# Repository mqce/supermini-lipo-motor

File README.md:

# supermini-lipo-motor

ESP32-C3 SuperMini の下に重ねる、2 モーター駆動と LiPo 充電の拡張基板です。外形は 18 × 24 mm、2 層です。回路図のリビジョンは 1（2026-11-01）です。

SuperMini のピンヘッダ（2.54 mm、左右 1×8）に合わせたスルーホールで接続します。電池、電源スイッチ、モーターは基板端の手はんだパッド（1.5 mm ピッチ、ドリル 0.7 mm）へ配線します。

## 電源

| ネット | 役割 |
| --- | --- |
| V5 | SuperMini の 5V。TP4056 の入力（USB 充電） |
| VBAT | LiPo 正極。TP4056 の BAT |
| VSW | モータードライバの電源。外部スイッチの負荷側 |
| GND | 共通グランド |

J3 の `SW_BAT`（VBAT）と `SW_LOAD`（VSW）のあいだに電源スイッチを入れます。スイッチを入れると電池が TC118S に供給されます。

D1（B5819W）はカソードが V5、アノードが VSW です。スイッチオンのとき電池から SuperMini の 5V ピンへ給電し、USB の 5V はモーター電源へ流れません。

TP4056 の PROG は 10 kΩ で、充電電流は約 120 mA です。CE は VCC、TEMP は GND に接続しています。充電中は LED1（赤）が点灯します。

## モーター

ドライバは Fuman TC118S が 2 個です。入力は 100 Ω を直列に入れています。

| モーター | INA | INB |
| --- | --- | --- |
| M1 | GPIO4 | GPIO3 |
| M2 | GPIO10 | GPIO7 |

GPIO2、GPIO8、GPIO9 は ESP32-C3 のストラップピンです。駆動に使わないでください。

## 手はんだパッド（J3、左から）

1. BAT+
2. BAT-
3. SW_BAT（VBAT）
4. SW_LOAD（VSW）
5. M1+
6. M1-
7. M2+
8. M2-

USB 側が基板の +Y 端です。部品面を上、USB を上にしたとき、5V 列が左側、GPIO5 列が右側です。

## ファイル

| パス | 内容 |
| --- | --- |
| `supermini-lipo-motor.kicad_pro` | KiCad 10 プロジェクト |
| `symbols/` `footprints/` | 独自シンボルとワイヤパッド |
| `tools/build_board.py` | 回路図・基板・BOM の生成スクリプト |
| `fabrication/` | JLCPCB 向け Gerber、BOM、座標 |
| `production/` | 製造データの別書き出し |

KiCad 10 で `supermini-lipo-motor.kicad_pro` を開きます。生成し直す場合は、KiCad 10 の `pcbnew` が使える Python で `tools/build_board.py` を実行します。スクリプト内のパスはローカル環境向けです。

JLCPCB へ出すときは `fabrication/jlcpcb-gerber.zip` と `fabrication/bom.csv`、`fabrication/cpl.csv` を使います。ヘッダ J1/J2 とワイヤパッド J3 は BOM に含まれません。

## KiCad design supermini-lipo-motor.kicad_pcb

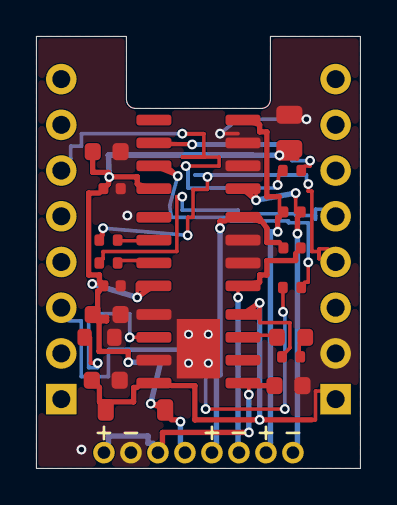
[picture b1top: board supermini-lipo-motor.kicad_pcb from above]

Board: 2 copper layers, 18.0 x 24.0 mm, 23 parts (0 on the bottom side), 19 nets.

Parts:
C1, C2, C3, C5: 10uF; C_0603_1608Metric
C4, C6, C7, C8: 100nF; C_0402_1005Metric
C9: 22uF; C_0805_2012Metric
D1: B5819W; D_SOD-123
J1: ESP_L; PTH_1x08_P2.54mm
J2: ESP_R; PTH_1x08_P2.54mm
J3: WIRES
LED1: RED; LED_0603_1608Metric
R1: 10k; R_0603_1608Metric
R2: 1k; R_0402_1005Metric
R3, R4, R5, R6: 100; R_0402_1005Metric
U1, U2: TC118S; SOIC-8_3.9x4.9mm_P1.27mm
U3: TP4056; SOIC-8-1EP_3.9x4.9mm_P1.27mm_EP2.41x3.3mm

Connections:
CHRG: LED1.1, U3.7
GND: C1.2, C2.2, C3.2, C4.2, C5.2, C6.2, C9.2, J1.2, J3.2, R1.2, U1.6, U1.7, U2.6, U2.7, U3.1, U3.3, U3.9
GPIO3: J1.5, R4.1
GPIO4: J1.4, R3.1
GPIO7: J2.3, R6.1
GPIO10: J2.6, R5.1
LED_A: LED1.2, R2.2
M1+: C7.1, J3.5, U1.8
M1-: C7.2, J3.6, U1.5
M1_INA: R3.2, U1.2
M1_INB: R4.2, U1.3
M2+: C8.1, J3.7, U2.8
M2-: C8.2, J3.8, U2.5
M2_INA: R5.2, U2.2
M2_INB: R6.2, U2.3
PROG: R1.1, U3.2
V5: C1.1, D1.1, J1.1, R2.1, U3.4, U3.8
VBAT: C2.1, J3.1, J3.3, U3.5
VSW: C3.1, C4.1, C5.1, C6.1, C9.1, D1.2, J3.4, U1.4, U2.4

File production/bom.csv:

Designator,Footprint,Quantity,Value,LCSC Part #
"C1, C2, C3, C5",0603,4,10uF,
"C4, C6, C7, C8",0402,4,100nF,
C9,0805,1,22uF,
D1,D_SOD-123,1,B5819W,
LED1,0603,1,RED,
R1,0603,1,10k,
R2,0402,1,1k,
"R3, R4, R5, R6",0402,4,100,
"U1, U2",SOIC-8_3.9x4.9mm_P1.27mm,2,TC118S,
U3,SOIC-8-1EP_3.9x4.9mm_P1.27mm_EP2.41x3.3mm,1,TP4056,

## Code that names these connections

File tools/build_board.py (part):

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                ("1", "5V", "passive"),
                ("2", "GND", "passive"),
                ("3", "3V3", "passive"),
                ("4", "GPIO4", "output"),
                ("5", "GPIO3", "output"),
                ("6", "GPIO2", "passive"),
                ("7", "GPIO1", "passive"),
                ("8", "GPIO0", "passive"),
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            [
                ("1", "GPIO5", "passive"),
                ("2", "GPIO6", "passive"),
                ("3", "GPIO7", "output"),
                ("4", "GPIO8", "passive"),
                ("5", "GPIO9", "passive"),
                ("6", "GPIO10", "output"),
                ("7", "GPIO20", "passive"),
                ("8", "GPIO21", "passive"),
            ]
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        sch.connect(world, "1", net1)
        sch.connect(world, "2", net2)

    two_pin("Device:R", "R1", "10k", r0603, 241.3, 165.1, "C25804", "PROG", "GND")
    two_pin("Device:R", "R2", "1k", r_fp, 355.6, 165.1, "C11702", "V5", "LED_A")
    two_pin("Device:R", "R3", "100", r_fp, 114.3, 215.9, "C25076", "GPIO4", "M1_INA")
    two_pin("Device:R", "R4", "100", r_fp, 114.3, 190.5, "C25076", "GPIO3", "M1_INB")
    two_pin("Device:R", "R5", "100", r_fp, 114.3, 139.7, "C25076", "GPIO10", "M2_INA")
    two_pin("Device:R", "R6", "100", r_fp, 114.3, 114.3, "C25076", "GPIO7", "M2_INB")
    two_pin("Device:C", "C1", "10uF", c0603, 355.6, 215.9, "C19702", "V5", "GND")
    two_pin("Device:C", "C2", "10uF", c0603, 355.6, 190.5, "C19702", "VBAT", "GND")
    two_pin("Device:C", "C3", "10uF", c0603, 215.9, 228.6, "C19702", "VSW", "GND")
    two_pin("Device:C", "C4", "100nF", c0402, 215.9, 203.2, "C1525", "VSW", "GND")
    two_pin("Device:C", "C5", "10uF", c0603, 215.9, 139.7, "C19702", "VSW", "GND")
    two_pin("Device:C", "C6", "100nF", c0402, 215.9, 114.3, "C1525", "VSW", "GND")
    two_pin("Device:C", "C7", "100nF", c0402, 215.9, 177.8, "C1525", "M1+", "M1-")
    two_pin("Device:C", "C8", "100nF", c0402, 215.9, 88.9, "C1525", "M2+", "M2-")
    two_pin("Device:C", "C9", "22uF", c0805, 215.9, 63.5, "C45783", "VSW", "GND")

    d1 = sch.add_symbol(
        "Device:D_Schottky",
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        "1": "V5",
        "2": "GND",
        "3": "NC",
        "4": "GPIO4",
        "5": "GPIO3",
        "6": "NC",
        "7": "NC",
        "8": "NC",
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    for number, net in {
        "1": "NC",
        "2": "NC",
        "3": "GPIO7",
        "4": "NC",
        "5": "NC",
        "6": "GPIO10",
        "7": "NC",
        "8": "NC",
    }.items():
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        sch.connect(flag, "1", net)

    sch.text("USB side of the stacked boards is the +Y edge.", 25.4, 215.9)
    sch.text("M1 INA=GPIO4 INB=GPIO3. M2 INA=GPIO10 INB=GPIO7.", 25.4, 210.82)
    sch.text("Do not drive GPIO2, GPIO8 or GPIO9.", 25.4, 205.74)

    content = "\n".join(
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    for pad in pads:
        if pad["net"]:
            groups.setdefault(pad["net"], []).append(pad)
    early = {"GPIO3", "GPIO4", "GPIO7", "GPIO10", "M1_INA", "M1_INB", "M2_INA", "PROG"}

    def rank(name):
        if name in early:
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        "M1_INB",
        "M2_INA",
        "M2_INB",
        "GPIO4",
        "GPIO3",
        "GPIO10",
        "GPIO7",
    ):
        N(name)

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    c9 = place(board, c0805, "C9", "22uF", 14.05, 5.30, 90, False)
    led = place(board, led_fp, "LED1", "RED", 14.15, 16.715, 0, False)

    j1_nets = ["V5", "GND", None, "GPIO4", "GPIO3", None, None, None]
    j2_nets = [None, None, "GPIO7", None, None, "GPIO10", None, None]
    j3_nets = ["VBAT", "GND", "VBAT", "VSW", "M1+", "M1-", "M2+", "M2-"]
    for index, net_name in enumerate(j1_nets, start=1):
        if net_name:
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    set_pad_net(led, "2", N("LED_A"))
    set_pad_net(led, "1", N("CHRG"))
    for fp, a, b in (
        (r3, "GPIO4", "M1_INA"),
        (r4, "GPIO3", "M1_INB"),
        (r5, "GPIO10", "M2_INA"),
        (r6, "GPIO7", "M2_INB"),
    ):
        set_pad_net(fp, "1", N(a))
        set_pad_net(fp, "2", N(b))
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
